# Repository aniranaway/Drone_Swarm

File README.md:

# Autonomous UWB Drone Swarm

A fully custom, low-level embedded hardware and firmware platform designed for autonomous multi drone swarms. The system integrates custom STM32-based flight controller PCBs, coreless DC motor drive arrays for a micro quadcopter form factor, Ultra-Wideband (UWB) 3D spatial localization, and custom control stacks built entirely from first principles—bypassing off-the-shelf flight controllers and third-party firmware stacks like PX4 or Betaflight.

---
## Grand Objectives

* **Bare-Metal Flight Control Stack:** Implement real-time 6-DoF sensor fusion and cascaded PID control loops running directly on STM32 microcontrollers.
* **Advanced State Estimation:** Design and implement a custom Extended Kalman Filter (EKF) pipeline to fuse multi-sensor measurements (IMU, Barometer, UWB), effectively suppressing sensor noise and drift for precise real-time 6-DoF state estimation.
* **UWB Spatial Positioning:** Achieve indoor positioning and tracking using UWB hardware operating across fixed anchor networks.
* **Autonomous Swarm Dynamics:** Execute coordinated multi-agent formation flight, collision avoidance algorithms, and telemetry links managed via a custom ground control station.
* **Rigorous Systems Engineering:** Maintain end-to-end engineering discipline across the full lifecycle—from System Requirements Documents (SRD) and component analysis to PCB layout, manufacturing, and firmware deployment.

## Project Documentation
Detailed engineering decisions and specifications are broken down in the `docs/` directory:
* [System Requirements Document (SRD)](docs/system_requirements.md)
* [Component Selection Analysis](docs/component_selection_analysis.md)
* [Bill of Materials (BOM)](docs/bill_of_materials.md)

---
## Repository Structure
* **/docs** - System engineering documents, trade studies, and requirements.
* **/hardware** - KiCad/Altium schematic captures and PCB layout files.
* **/firmware** - STM32 C/C++ application logic (CMake/Ninja toolchain).

## Development Roadmap

This project follows a structured hardware-software co-design lifecycle, progressing from systems engineering and hardware fabrication to low-level control, state estimation, and multi-agent coordination:

- [X] **Phase 1: Requirements & Component Selection** *(Completed)*  
  Establish System Requirements Documents (SRD), execute trade studies for core components (MCU, IMU, UWB, Power), and calculate mass/power budgets.

- [X] **Phase 2: Schematic Capture & Circuit Design**  *(Completed)* 
  Design power regulation, coreless motor MOSFET drive arrays, RF layout rules for radio, SWD interfaces, sensor layouts, and dedicated test pads.

- [ ] **Phase 3: PCB Layout, Manufacturing & Board Bring-Up**  (In Progress)
  Perform 4-layer PCB layout with impedance matching, manage fabrication/assembly, and execute board bring-up (power rail verification, current draw checks, and SWD flashing).

- [ ] **Phase 4: Low-Level Drivers & Telemetry Baseline**  
  Develop register-level/HAL SPI drivers for the IMU, I2C drivers for the barometer, PWM timer outputs for motor control, UART telemetry output, and status LED error handlers.

- [ ] **Phase 5: Airframe Assembly & Hardware Integration**  
  Mount flight controllers to micro frames, wire motor connections, calibrate motor spin directions, and verify physical center of mass.

- [ ] **Phase 6: Advanced State Estimation & Flight Control**  
  Implement digital low-pass filtering, build a custom Extended Kalman Filter (EKF) pipeline for IMU/Baro/UWB fusion, write cascaded PID controllers, and perform tethered flight tuning.

- [ ] **Phase 7: Swarm Simulation & Waypoint Planning**  
  Develop simulation frameworks and Ground Control Station (GCS) telemetry interfaces to validate trajectory generation and collision avoidance prior to physical swarm deployment.

- [ ] **Phase 8: UWB Infrastructure & Multi-Agent Setup**  
  Deploy and calibrate fixed indoor UWB anchors, assemble secondary flight hardware, and establish inter-node wireless communications.

- [ ] **Phase 9: Swarm Coordination & Autonomous Flight**  
  Execute decentralized/centralized swarm algorithms for coordinated formation flight, multi-agent pathing, and real-time telemetry tracking.

---
## Core Toolchain & Software Stack
* **GNU Arm Embedded Toolchain (`arm-none-eabi-gcc`)** — Cross-compiler toolchain used to compile bare-metal C/C++ application logic into ARM Cortex-M machine code.
* **CMake** — Meta-build system used to manage cross-compilation targets, include directories, linker scripts (`.ld`), and hardware macros in a clean, maintainable structure.
* **Ninja** — High-speed build system executed by CMake to handle fast, parallelized incremental compilation.
* **STM32CubeMX** — Graphical initialization utility used to configure MCU clock trees, pin assignments, and hardware peripherals (SPI, I2C, UART, TIM) while generating isolated HAL setup files.
* **OpenOCD** — Open On-Chip Debugger used to flash binary targets (`.elf`/`.hex`) to the STM32 MCU and provide a live GDB server over Serial Wire Debug (SWD) via ST-LINK.
* **VS Code & Cortex-Debug** — Primary IDE environment leveraging the Cortex-Debug extension for hardware breakpoints, register inspection, and integrated CMake builds.

---
## Core Hardware Stack
* **Microcontroller:** (In Progress - See Component Selection Analysis)
* **Spatial Positioning:** (In Progress - See Component Selection Analysis)
* **IMU:** (In Progress - See Component Selection Analysis)
* **Barometer:** (In Progress - See Component Selection Analysis)
* **Power:** (In Progress - See Component Selection Analysis)

---
## Getting Started
*(Instructions for cloning, compiling with CMake, and flashing the STM32 will go here).*

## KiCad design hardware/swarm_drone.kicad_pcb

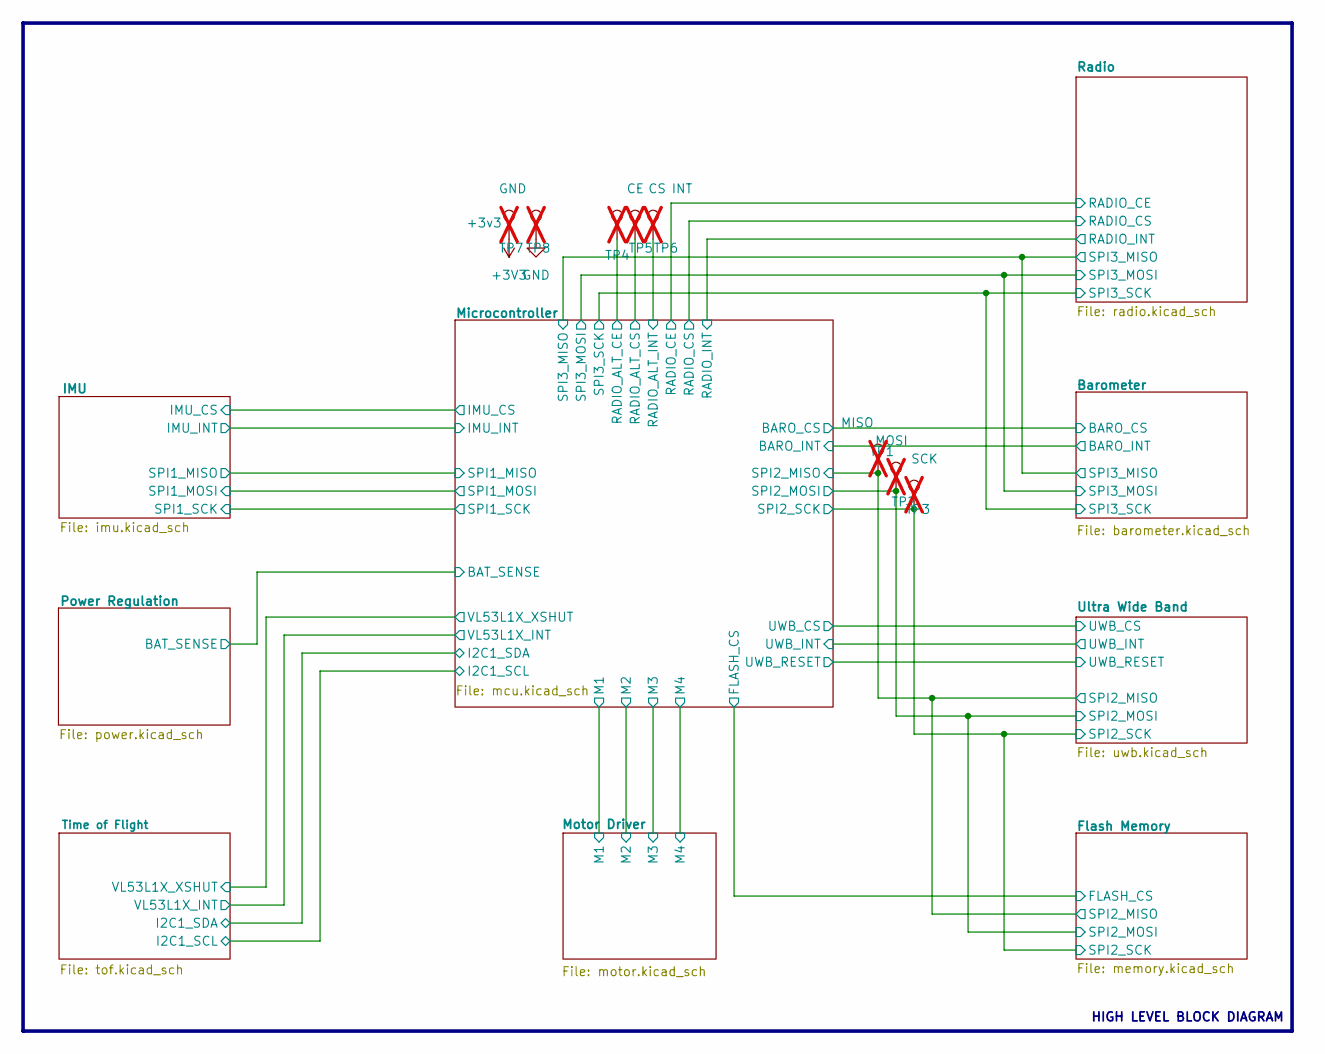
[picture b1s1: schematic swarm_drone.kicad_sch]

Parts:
TP1: MISO; TestPoint_Pad_1.0x1.0mm; not fitted
TP2: MOSI; TestPoint_Pad_1.0x1.0mm; not fitted
TP3: SCK; TestPoint_Pad_1.0x1.0mm; not fitted
TP4: CE; TestPoint_Pad_1.0x1.0mm; not fitted
TP5: CS; TestPoint_Pad_1.0x1.0mm; not fitted
TP6: INT; TestPoint_Pad_1.0x1.0mm; not fitted
TP7: +3v3; TestPoint_Pad_1.0x1.0mm; not fitted
TP8: GND; TestPoint_Pad_1.0x1.0mm; not fitted

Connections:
+3V3: TP7.1 (1_1); also elsewhere on the board
/Flash Memory/SPI2_MISO: TP1.1 (1_1); also elsewhere on the board
/Flash Memory/SPI2_MOSI: TP2.1 (1_1); also elsewhere on the board
/Flash Memory/SPI2_SCK: TP3.1 (1_1); also elsewhere on the board
/Microcontroller/RADIO_ALT_CE: TP4.1 (1_1); also elsewhere on the board
/Microcontroller/RADIO_ALT_CS: TP5.1 (1_1); also elsewhere on the board
/Microcontroller/RADIO_ALT_INT: TP6.1 (1_1); also elsewhere on the board
GND: TP8.1 (1_1); also elsewhere on the board

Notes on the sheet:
HIGH LEVEL BLOCK DIAGRAM

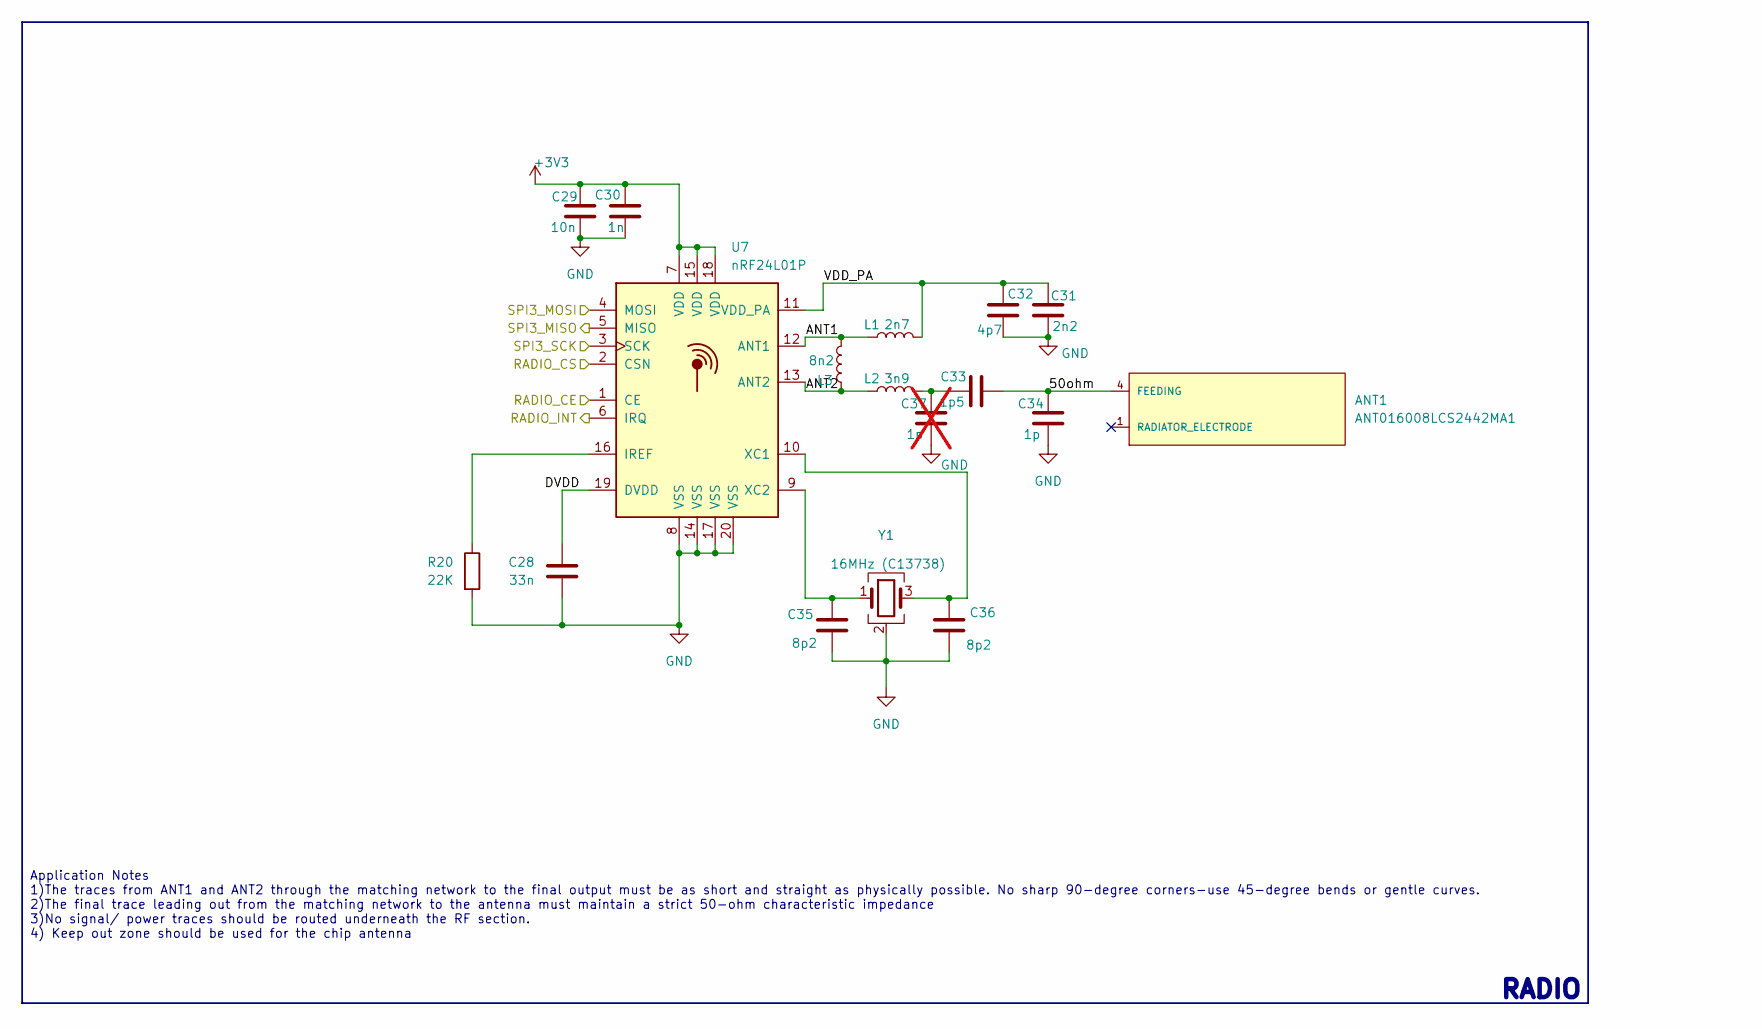
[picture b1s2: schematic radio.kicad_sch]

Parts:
ANT1: ANT016008LCS2442MA1; ANT_ANT016008LCS2442MA1; PARTREV sep 2016; LCSC C76585
C28: 33n; C_0603_1608Metric; LCSC C21117
C29: 10n; C_0402_1005Metric; LCSC C15195
C30: 1n; C_0402_1005Metric; LCSC C1523
C31: 2n2; C_0603_1608Metric; LCSC C1604
C32: 4p7; C_0402_1005Metric; LCSC C1569
C33: 1p5; C_0402_1005Metric; LCSC C1552
C34: 1p; C_0402_1005Metric; LCSC C1550
C35, C36: 8p2; C_0402_1005Metric; LCSC C1579
C37: 1p; C_0402_1005Metric; not fitted
L1: 2n7; L_0402_1005Metric
L2: 3n9; L_0402_1005Metric
L3: 8n2; L_0402_1005Metric
R20: 22K; R_0402_1005Metric; LCSC C25768
U7: nRF24L01P; QFN-20-1EP_4x4mm_P0.5mm_EP2.5x2.5mm; LCSC C8791
Y1: 16MHz (C13738); Crystal_SMD_3225-4Pin_3.2x2.5mm; LCSC C13738

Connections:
+3V3: C29.1, C30.1, U7.7 (VDD), U7.15 (VDD), U7.18 (VDD); also elsewhere on the board
/Barometer/SPI3_MISO: U7.5 (MISO); also elsewhere on the board
/Barometer/SPI3_MOSI: U7.4 (MOSI); also elsewhere on the board
/Barometer/SPI3_SCK: U7.3 (SCK); also elsewhere on the board
/Microcontroller/RADIO_CE: U7.1 (CE); also elsewhere on the board
/Microcontroller/RADIO_CS: U7.2 (CSN); also elsewhere on the board
/Microcontroller/RADIO_INT: U7.6 (IRQ); also elsewhere on the board
/Radio/50ohm: ANT1.4 (FEEDING_4), C33.2, C34.2
/Radio/ANT1: L1.1, L3.2, U7.12 (ANT1)
/Radio/ANT2: L2.1, L3.1, U7.13 (ANT2)
/Radio/DVDD: C28.1, U7.19 (DVDD)
/Radio/VDD_PA: C31.1, C32.1, L1.2, U7.11 (VDD_PA)
GND: C28.2, C29.2, C30.2, C31.2, C32.2, C34.1, C35.2, C36.2, C37.1, R20.2, U7.8 (VSS), U7.14 (VSS), U7.17 (VSS), U7.20 (VSS), Y1.2 (G), Y1.4 (G); also elsewhere on the board
unnamed: C33.1, C37.2, L2.2
unnamed: R20.1, U7.16 (IREF)
unnamed: C36.1, U7.10 (XC1), Y1.3
unnamed: C35.1, U7.9 (XC2), Y1.1

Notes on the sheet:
RADIO
Application Notes 1)The traces from ANT1 and ANT2 through the matching network to the final output must be as short and straight as physically possible. No sharp 90-degree corners-use 45-degree bends or gentle curves. 2)The final trace leading out from the matching network to the antenna must maint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

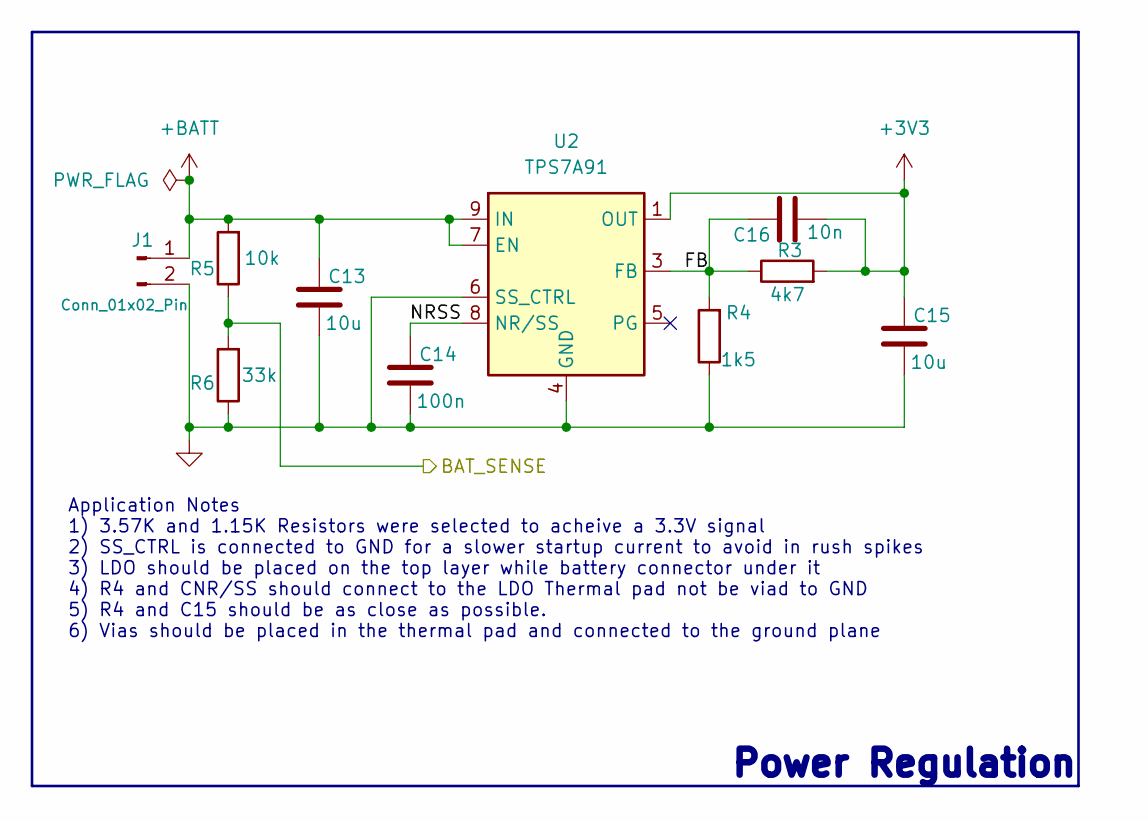
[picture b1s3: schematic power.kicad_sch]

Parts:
C13, C15: 10u; C_0603_1608Metric; LCSC C19702
C14: 100n; C_0402_1005Metric; LCSC C1525
C16: 10n; C_0402_1005Metric; LCSC C15195
J1: Conn_01x02_Pin; JST_PH_S2B-PH-K_1x02_P2.00mm_Horizontal; LCSC C173752
R3: 4k7; R_0402_1005Metric; LCSC C25900
R4: 1k5; R_0402_1005Metric; LCSC C25867
R5: 10k; R_0402_1005Metric; LCSC C25744
R6: 33k; R_0402_1005Metric; LCSC C25779
U2: TPS7A91; Texas_S-PDSO-N10_EP1.2x2mm_ThermalVias; LCSC C969024

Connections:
+3V3: C15.1, C16.2, R3.2, U2.1 (OUT), U2.2 (OUT); also elsewhere on the board
+BATT: C13.1, J1.1, R5.2, U2.7 (EN), U2.9 (IN), U2.10 (IN); also elsewhere on the board
/Microcontroller/BAT_SENSE: R5.1, R6.2; also elsewhere on the board
/Power Regulation/FB: C16.1, R3.1, R4.2, U2.3 (FB)
/Power Regulation/NRSS: C14.1, U2.8 (NR/SS)
GND: C13.2, C14.2, C15.2, J1.2, R4.1, R6.1, U2.4 (GND), U2.6 (SS_CTRL), U2.11 (GND); also elsewhere on the board

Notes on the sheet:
Application Notes 1) 3.57K and 1.15K Resistors were selected to acheive a 3.3V signal 2) SS_CTRL is connected to GND for a slower startup current to avoid in rush spikes 3) LDO should be placed on the top layer while battery connector under it 4) R4 and CNR/SS should connect to the LDO Thermal pad 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
Power Regulation

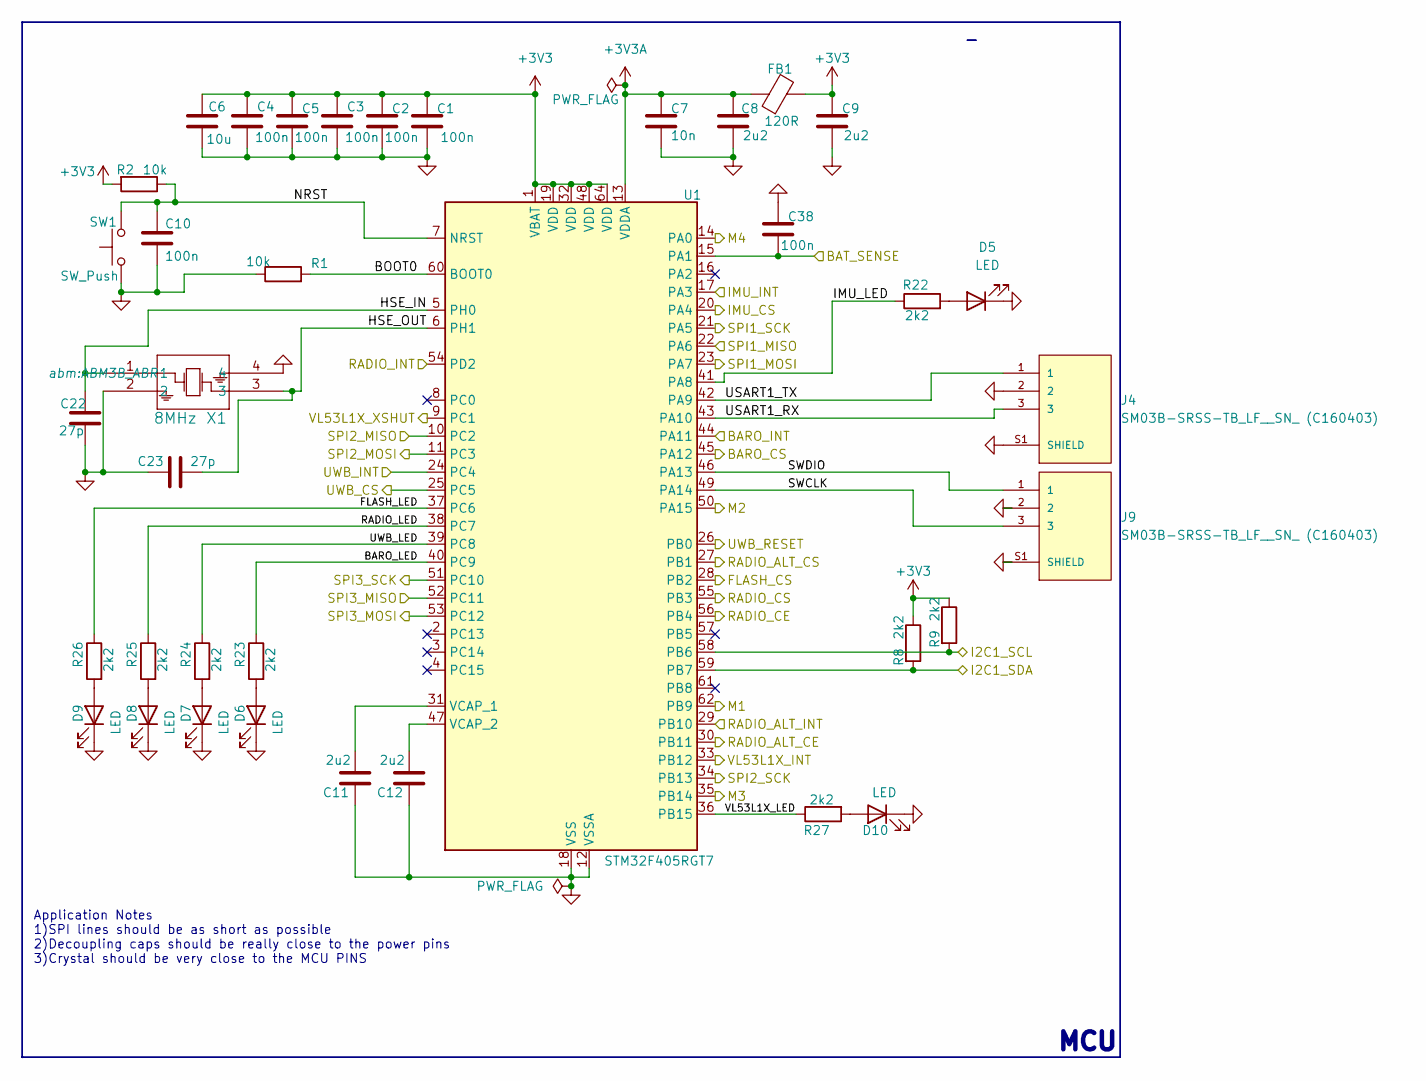
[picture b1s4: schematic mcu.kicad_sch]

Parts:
C1, C2, C3, C4, C5, C10, C38: 100n; C_0402_1005Metric; LCSC C1525
C6: 10u; C_0603_1608Metric; LCSC C19702
C7: 10n; C_0402_1005Metric; LCSC C15195
C8, C9, C11, C12: 2u2; C_0402_1005Metric; LCSC C12530
C22, C23: 27p; C_0402_1005Metric; LCSC C1557
D5, D6, D7, D8, D9, D10: LED; LED_0603_1608Metric; LCSC C2286
FB1: 120R; L_0603_1608Metric; LCSC C14709
J4, J9: SM03B-SRSS-TB_LF__SN_ (C160403); JST_SM03B-SRSS-TB_LF__SN_; LCSC C160403
R1, R2: 10k; R_0402_1005Metric; LCSC C25744
R8, R9, R22, R23, R24, R25, R26, R27: 2k2; R_0402_1005Metric; LCSC C25879
SW1: SW_Push; SW_SPST_TS-1088-xR020; LCSC C720477
U1: STM32F405RGT7; LQFP-64_10x10mm_P0.5mm; LCSC C1337199
X1: 8MHz; ABM3B_ABR; LCSC C83312

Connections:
+3V3: C1.1, C2.1, C3.1, C4.1, C5.1, C6.1, C9.1, FB1.2, R2.2, R8.1, R9.1, U1.1 (VBAT), U1.19 (VDD), U1.32 (VDD), U1.48 (VDD), U1.64 (VDD); also elsewhere on the board
+3V3A: C7.1, C8.1, FB1.1, U1.13 (VDDA)
/Barometer/BARO_CS: U1.45 (PA12); also elsewhere on the board
/Barometer/BARO_INT: U1.44 (PA11); also elsewhere on the board
/Barometer/SPI3_MISO: U1.52 (PC11); also elsewhere on the board
/Barometer/SPI3_MOSI: U1.53 (PC12); also elsewhere on the board
/Barometer/SPI3_SCK: U1.51 (PC10); also elsewhere on the board
/Flash Memory/FLASH_CS: U1.28 (PB2); also elsewhere on the board
/Flash Memory/SPI2_MISO: U1.10 (PC2); also elsewhere on the board
/Flash Memory/SPI2_MOSI: U1.11 (PC3); also elsewhere on the board
/Flash Memory/SPI2_SCK: U1.34 (PB13); also elsewhere on the board
/IMU/IMU_CS: U1.20 (PA4); also elsewhere on the board
/IMU/IMU_INT: U1.17 (PA3); also elsewhere on the board
/IMU/SPI1_MISO: U1.22 (PA6); also elsewhere on the board
/IMU/SPI1_MOSI: U1.23 (PA7); also elsewhere on the board
/IMU/SPI1_SCK: U1.21 (PA5); also elsewhere on the board
/Microcontroller/BARO_LED: R23.1, U1.40 (PC9)
/Microcontroller/BAT_SENSE: C38.2, U1.15 (PA1); also elsewhere on the board
/Microcontroller/BOOT0: R1.2, U1.60 (BOOT0)
/Microcontroller/FLASH_LED: R26.1, U1.37 (PC6)
/Microcontroller/HSE_IN: C22.1, U1.5 (PH0), X1.1
/Microcontroller/HSE_OUT: C23.2, U1.6 (PH1), X1.3
/Microcontroller/I2C1_SCL: R9.2, U1.58 (PB6); also elsewhere on the board
/Microcontroller/I2C1_SDA: R8.2, U1.59 (PB7); also elsewhere on the board
/Microcontroller/IMU_LED: R22.1, U1.41 (PA8)
/Microcontroller/M1: U1.62 (PB9); also elsewhere on the board
/Microcontroller/M2: U1.50 (PA15); also elsewhere on the board
/Microcontroller/M3: U1.35 (PB14); also elsewhere on the board
/Microcontroller/M4: U1.14 (PA0); also elsewhere on the board
/Microcontroller/NRST: C10.1, R2.1, SW1.2, U1.7 (NRST)
/Microcontroller/RADIO_ALT_CE: U1.30 (PB11); also elsewhere on the board
/Microcontroller/RADIO_ALT_CS: U1.27 (PB1); also elsewhere on the board
/Microcontroller/RADIO_ALT_INT: U1.29 (PB10); also elsewhere on the board
/Microcontroller/RADIO_CE: U1.56 (PB4); also elsewhere on the board
/Microcontroller/RADIO_CS: U1.55 (PB3); also elsewhere on the board
/Microcontroller/RADIO_INT: U1.54 (PD2); also elsewhere on the board
/Microcontroller/RADIO_LED: R25.1, U1.38 (PC7)
/Microcontroller/SWCLK: J9.3, U1.49 (PA14)
/Microcontroller/SWDIO: J9.1, U1.46 (PA13)
/Microcontroller/USART1_RX: J4.3, U1.43 (PA10)
/Microcontroller/USART1_TX: J4.1, U1.42 (PA9)
/Microcontroller/UWB_CS: U1.25 (PC5); also elsewhere on the board
/Microcontroller/UWB_INT: U1.24 (PC4); also elsewhere on the board
/Microcontroller/UWB_LED: R24.1, U1.39 (PC8)
/Microcontroller/UWB_RESET: U1.26 (PB0); also elsewhere on the board
/Microcontroller/VL53L1X_INT: U1.33 (PB12); also elsewhere on the board
/Microcontroller/VL53L1X_LED: R27.1, U1.36 (PB15)
/Microcontroller/VL53L1X_XSHUT: U1.9 (PC1); also elsewhere on the board
GND: C1.2, C2.2, C3.2, C4.2, C5.2, C6.2, C7.2, C8.2, C9.2, C10.2, C11.1, C12.1, C22.2, C23.1, C38.1, D5.1 (K), D6.1 (K), D7.1 (K), D8.1 (K), D9.1 (K), D10.1 (K), J4.2, J4.S1 (SHIELD), J4.S2 (SHIELD), J9.2, J9.S1 (SHIELD), J9.S2 (SHIELD), R1.1, SW1.1, U1.12 (VSSA), U1.18 (VSS), U1.63 (VSS), X1.2, X1.4; also elsewhere on the board
unnamed: D5.2 (A), R22.2
unnamed: D6.2 (A), R23.2
unnamed: D7.2 (A), R24.2
unnamed: D8.2 (A), R25.2
unnamed: D9.2 (A), R26.2
unnamed: D10.2 (A), R27.2
unnamed: C11.2, U1.31 (VCAP_1)
unnamed: C12.2, U1.47 (VCAP_2)

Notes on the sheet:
Application Notes 1)SPI lines should be as short as possible 2)Decoupling caps should be really close to the power pins 3)Crystal should be very close to the MCU PINS
MCU

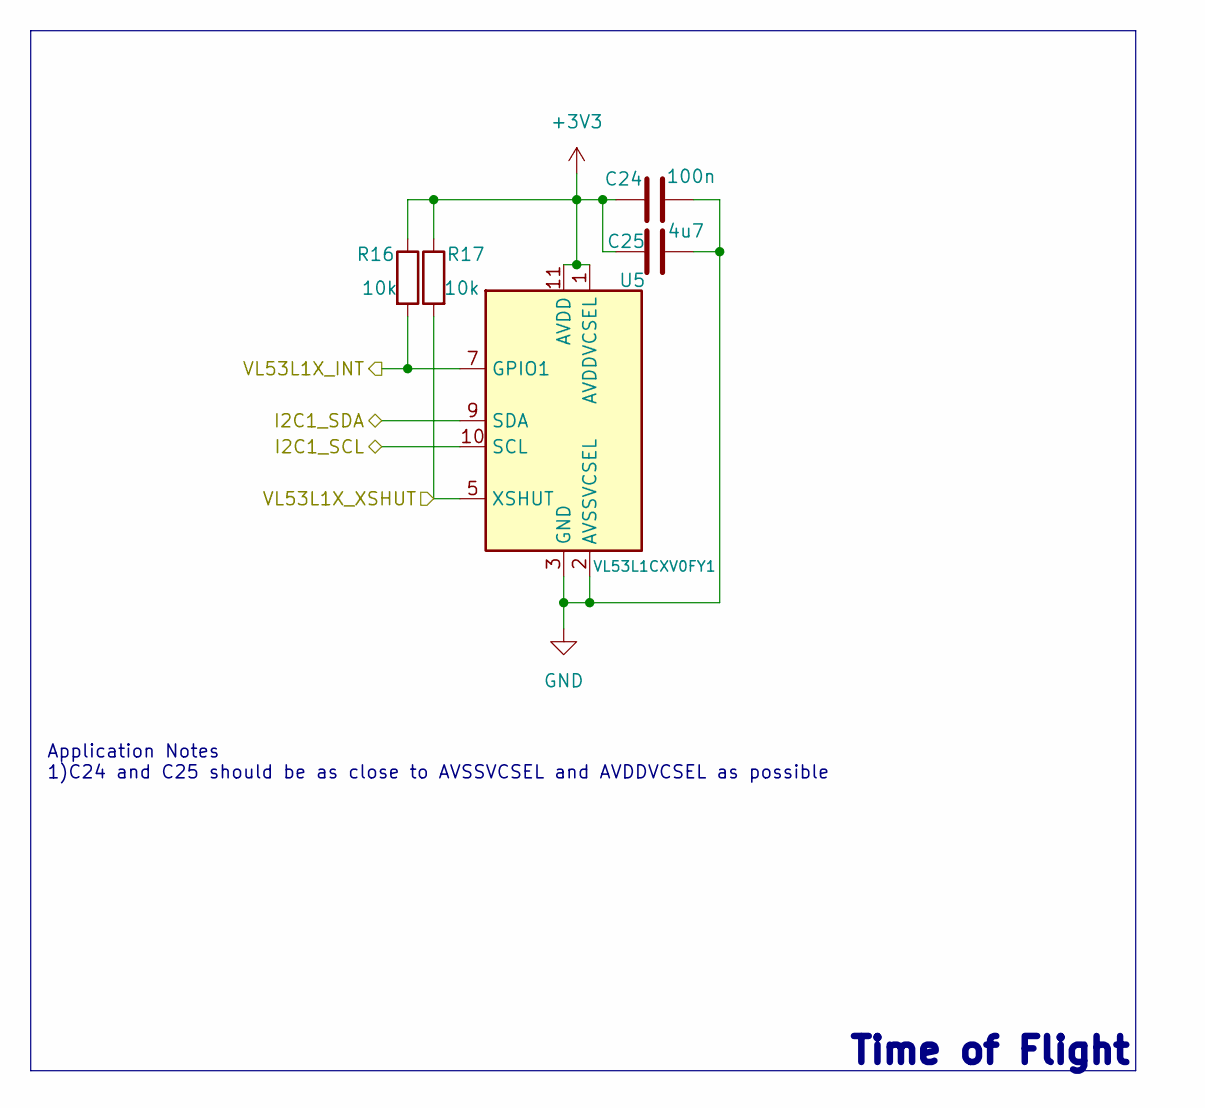
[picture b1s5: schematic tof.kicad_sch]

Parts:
C24: 100n; C_0402_1005Metric; LCSC C1525
C25: 4u7; C_0603_1608Metric; LCSC C19666
R16, R17: 10k; R_0402_1005Metric; LCSC C25744
U5: VL53L1CXV0FY1; ST_VL53L1x; LCSC C190004

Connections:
+3V3: C24.1, C25.1, R16.1, R17.1, U5.1 (AVDDVCSEL), U5.11 (AVDD); also elsewhere on the board
/Microcontroller/I2C1_SCL: U5.10 (SCL); also elsewhere on the board
/Microcontroller/I2C1_SDA: U5.9 (SDA); also elsewhere on the board
/Microcontroller/VL53L1X_INT: R16.2, U5.7 (GPIO1); also elsewhere on the board
/Microcontroller/VL53L1X_XSHUT: R17.2, U5.5 (XSHUT); also elsewhere on the board
GND: C24.2, C25.2, U5.2 (AVSSVCSEL), U5.3 (GND), U5.4 (GND), U5.6 (GND), U5.12 (GND); also elsewhere on the board

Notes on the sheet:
Application Notes 1)C24 and C25 should be as close to AVSSVCSEL and AVDDVCSEL as possible
Time of Flight

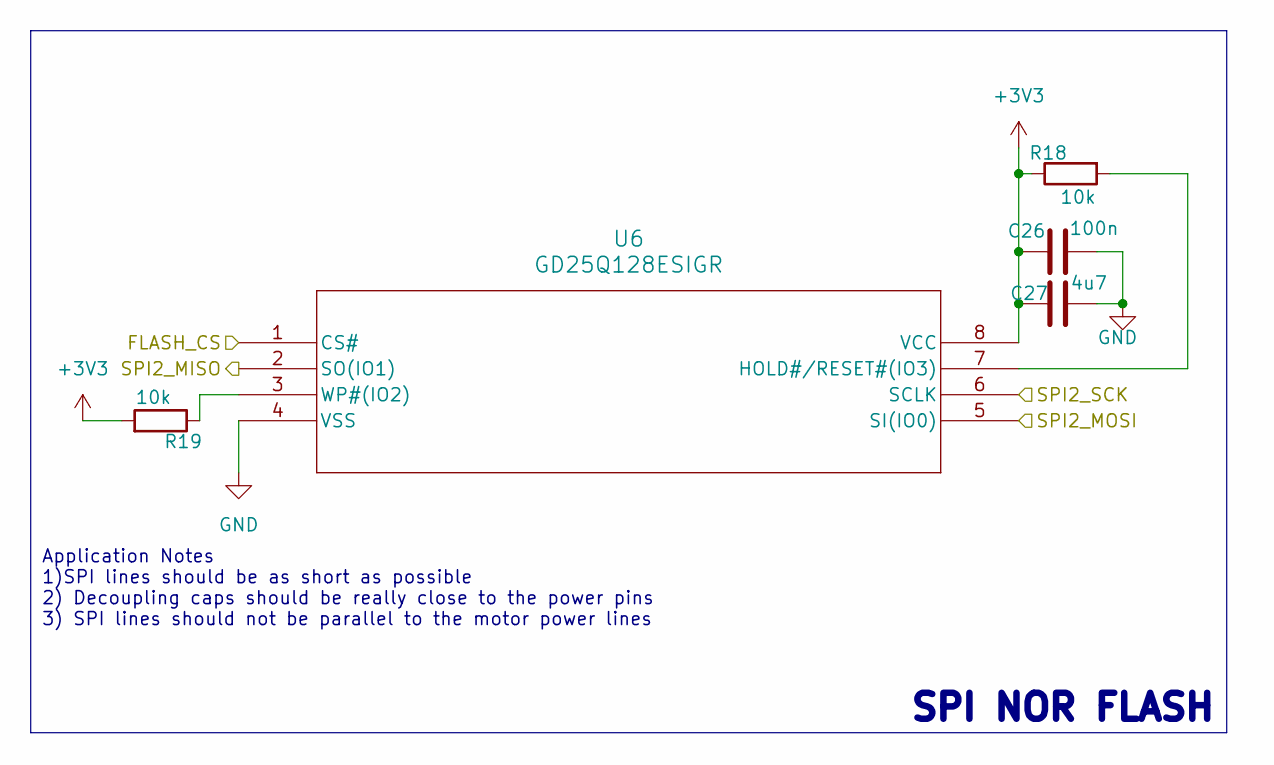
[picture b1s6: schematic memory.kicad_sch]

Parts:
C26: 100n; C_0402_1005Metric; LCSC C1525
C27: 4u7; C_0603_1608Metric; LCSC C19666
R18, R19: 10k; R_0402_1005Metric; LCSC C25744
U6: GD25Q128ESIGR; SOP8_208MIL_GDV; LCSC C2928891

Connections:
+3V3: C26.1, C27.1, R18.1, R19.2, U6.8 (VCC); also elsewhere on the board
/Flash Memory/FLASH_CS: U6.1 (CS#); also elsewhere on the board
/Flash Memory/SPI2_MISO: U6.2 (SO(IO1)); also elsewhere on the board
/Flash Memory/SPI2_MOSI: U6.5 (SI(IO0)); also elsewhere on the board
/Flash Memory/SPI2_SCK: U6.6 (SCLK); also elsewhere on the board
GND: C26.2, C27.2, U6.4 (VSS); also elsewhere on the board
unnamed: R18.2, U6.7 (HOLD#/RESET#(IO3))
unnamed: R19.1, U6.3 (WP#(IO2))

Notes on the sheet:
SPI NOR FLASH
Application Notes 1)SPI lines should be as short as possible 2) Decoupling caps should be really close to the power pins 3) SPI lines should not be parallel to the motor power lines

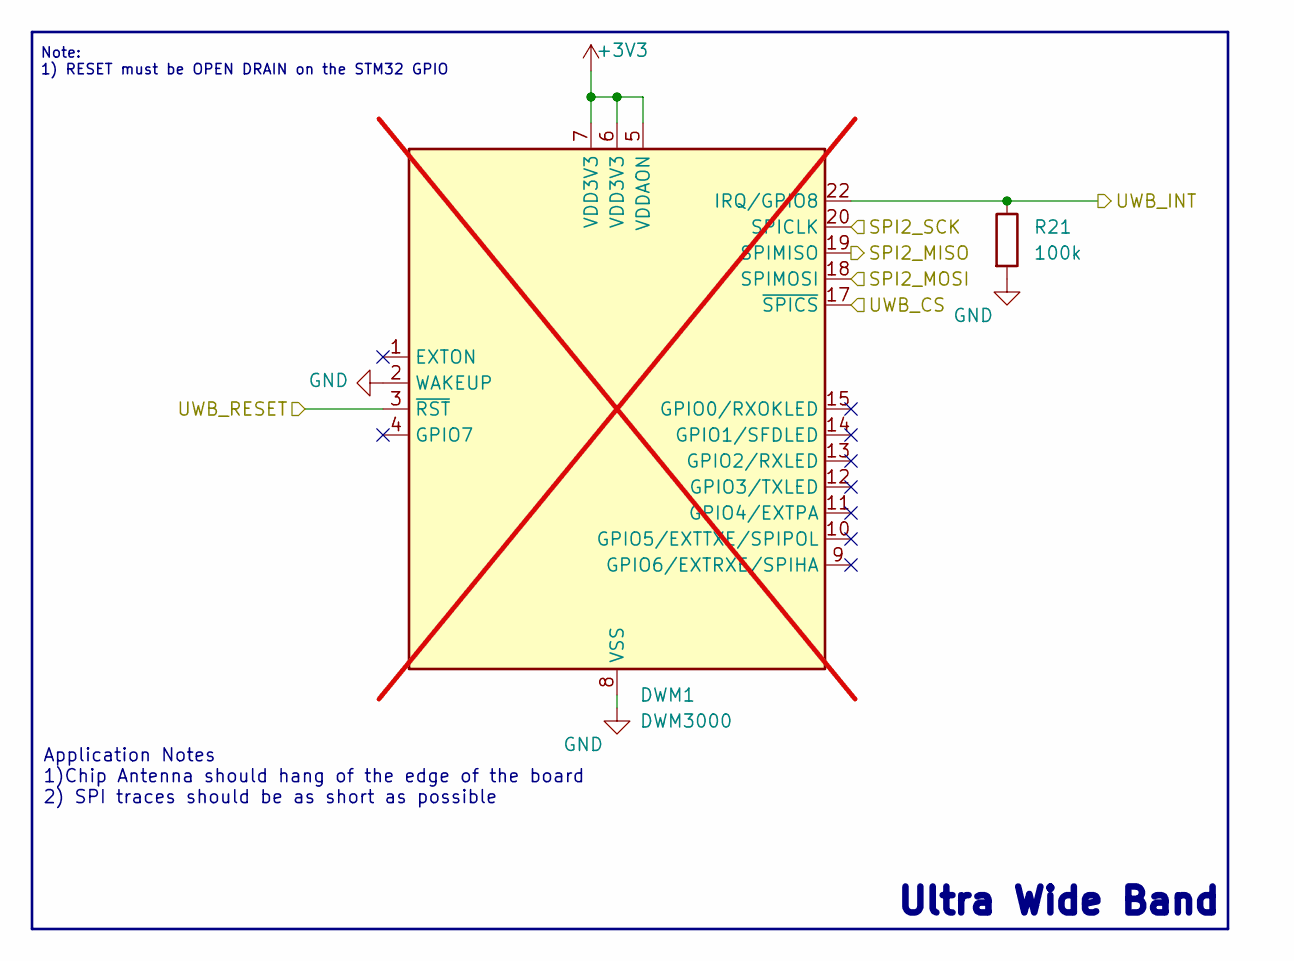
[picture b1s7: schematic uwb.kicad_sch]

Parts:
DWM1: DWM3000; DWM1000; not fitted
R21: 100k; R_0402_1005Metric; LCSC C25741

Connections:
+3V3: DWM1.5 (VDDAON), DWM1.6 (VDD3V3), DWM1.7 (VDD3V3); also elsewhere on the board
/Flash Memory/SPI2_MISO: DWM1.19 (SPIMISO); also elsewhere on the board
/Flash Memory/SPI2_MOSI: DWM1.18 (SPIMOSI); also elsewhere on the board
/Flash Memory/SPI2_SCK: DWM1.20 (SPICLK); also elsewhere on the board
/Microcontroller/UWB_CS: DWM1.17 (~SPICS); also elsewhere on the board
/Microcontroller/UWB_INT: DWM1.22 (IRQ/GPIO8), R21.1; also elsewhere on the board
/Microcontroller/UWB_RESET: DWM1.3 (~RST); also elsewhere on the board
GND: DWM1.2 (WAKEUP), DWM1.8 (VSS), DWM1.16 (VSS), DWM1.21 (VSS), DWM1.23 (VSS), DWM1.24 (VSS), R21.2; also elsewhere on the board

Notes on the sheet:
Application Notes 1)Chip Antenna should hang of the edge of the board 2) SPI traces should be as short as possible
Ultra Wide Band
Note: 1) RESET must be OPEN DRAIN on the STM32 GPIO

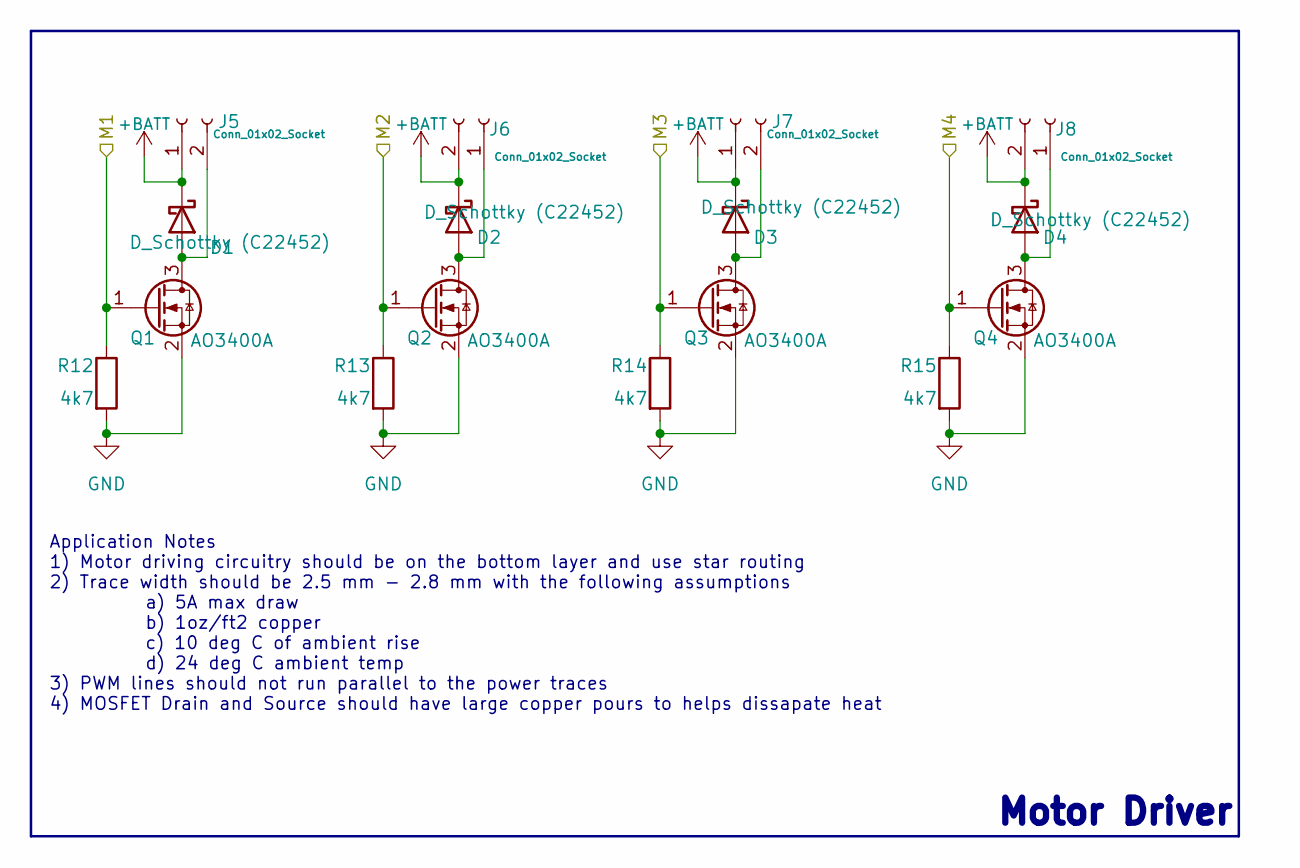
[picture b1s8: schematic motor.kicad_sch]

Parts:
D1, D2, D3, D4: D_Schottky (C22452); D_SMA; LCSC C22452
J5, J6, J7, J8: Conn_01x02_Socket; JST_S2B-ZR-3.4_LF__SN_; LCSC C160729
Q1, Q2, Q3, Q4: AO3400A; SOT-23; LCSC C20917
R12, R13, R14, R15: 4k7; R_0402_1005Metric; LCSC C25900

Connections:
+BATT: D1.1 (K), D2.1 (K), D3.1 (K), D4.1 (K), J5.1, J6.2, J7.1, J8.2; also elsewhere on the board
/Microcontroller/M1: Q1.1 (G), R12.1; also elsewhere on the board
/Microcontroller/M2: Q2.1 (G), R13.1; also elsewhere on the board
/Microcontroller/M3: Q3.1 (G), R14.1; also elsewhere on the board
/Microcontroller/M4: Q4.1 (G), R15.1; also elsewhere on the board
GND: Q1.2 (S), Q2.2 (S), Q3.2 (S), Q4.2 (S), R12.2, R13.2, R14.2, R15.2; also elsewhere on the board
unnamed: D1.2 (A), J5.2, Q1.3 (D)
unnamed: D2.2 (A), J6.1, Q2.3 (D)
unnamed: D3.2 (A), J7.2, Q3.3 (D)
unnamed: D4.2 (A), J8.1, Q4.3 (D)

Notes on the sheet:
Application Notes 1) Motor driving circuitry should be on the bottom layer and use star routing 2) Trace width should be 2.5 mm - 2.8 mm with the following assumptions a) 5A max draw b) 1oz/ft2 copper c) 10 deg C of ambient rise d) 24 deg C ambient temp 3) PWM lines should not run parallel to the p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
Motor Driver

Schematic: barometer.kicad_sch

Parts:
C20, C21: 100n; C_0402_1005Metric; LCSC C1525
U4: BMP581; QFN10_BMP581_BOS; LCSC C5362283

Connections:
+3V3: C20.1, C21.1, U4.1 (VDDIO), U4.10 (VDD); also elsewhere on the board
/Barometer/BARO_CS: U4.6 (CSB); also elsewhere on the board
/Barometer/BARO_INT: U4.7 (INT); also elsewhere on the board
/Barometer/SPI3_MISO: U4.5 (SDO); also elsewhere on the board
/Barometer/SPI3_MOSI: U4.4 (SDI); also elsewhere on the board
/Barometer/SPI3_SCK: U4.2 (SCK); also elsewhere on the board
GND: C20.2, C21.2, U4.3 (VSS), U4.8 (VSS), U4.9 (VSS); also elsewhere on the board

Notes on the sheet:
Application Notes 1) Barometer should be placed on the central axis of the PCB to avoid pressure drops from the motors 2) Barometer should be placed away from high heat components 3) Barometer should not be placed near the very edge of the PCB to avoid twisiting forces adding noise
Barometer

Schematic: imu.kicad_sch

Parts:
C17: 100n; C_0402_1005Metric; LCSC C1525
C18: 2u2; C_0402_1005Metric; LCSC C12530
C19: 10n; C_0402_1005Metric; LCSC C15195
R7: 10k; R_0402_1005Metric; LCSC C25744
U3: ICM-42688-P; PQFN50P300X250X97-14N; PARTREV 1.2; LCSC C1850418

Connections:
+3V3: C17.1, C18.1, C19.1, R7.2, U3.5 (VDDIO), U3.8 (VDD); also elsewhere on the board
/IMU/IMU_CS: R7.1, U3.12 (AP_CS); also elsewhere on the board
/IMU/IMU_INT: U3.4 (INT1/INT); also elsewhere on the board
/IMU/SPI1_MISO: U3.1 (AP_SDO/AP_AD0); also elsewhere on the board
/IMU/SPI1_MOSI: U3.14 (AP_SDA/AP_SDIO/AP_SDI); also elsewhere on the board
/IMU/SPI1_SCK: U3.13 (AP_SCL/AP_SCLK); also elsewhere on the board
GND: C17.2, C18.2, C19.2, U3.2 (RESV_2), U3.3 (RESV_3), U3.6 (GND), U3.7 (RESV_7), U3.9 (INT2/FSYNC/CLKIN), U3.10 (RESV_10), U3.11 (RESV_11); also elsewhere on the board

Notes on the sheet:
Application Notes 1) IMU Shoulde be placed as close to the geometric centre of the PCB as possible 2) IMU should not be placed near high heat components 3) decoupling caps should be placed very close to power pins
IMU

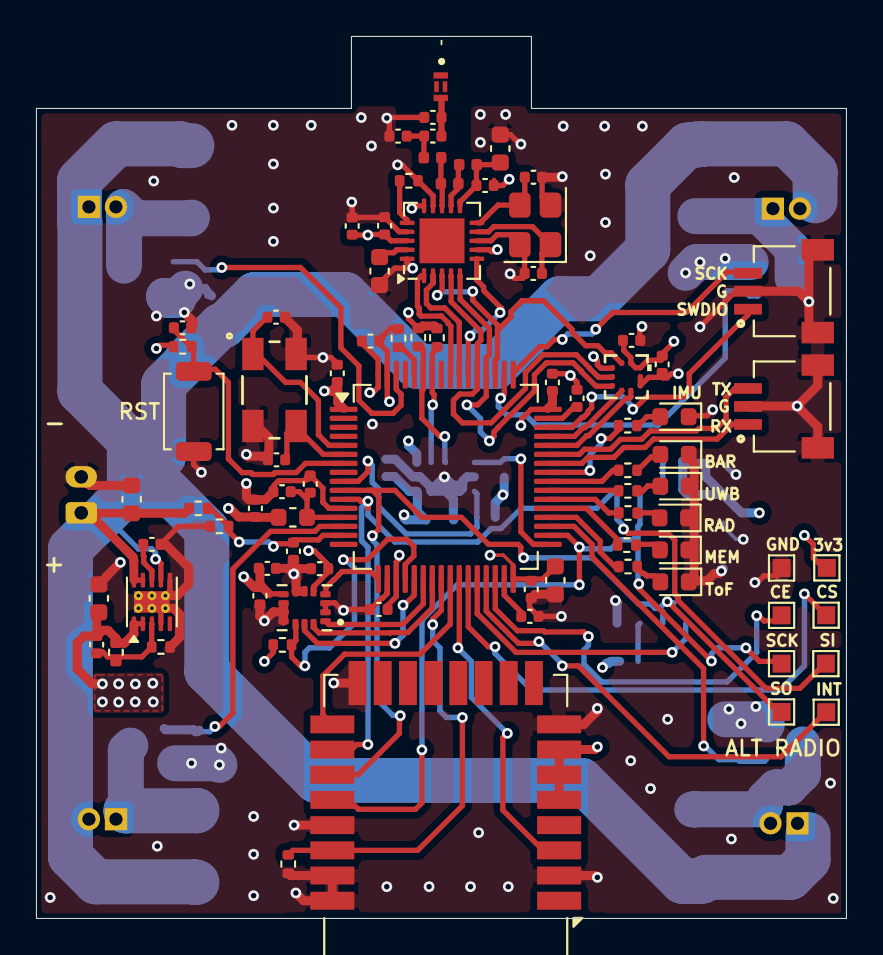
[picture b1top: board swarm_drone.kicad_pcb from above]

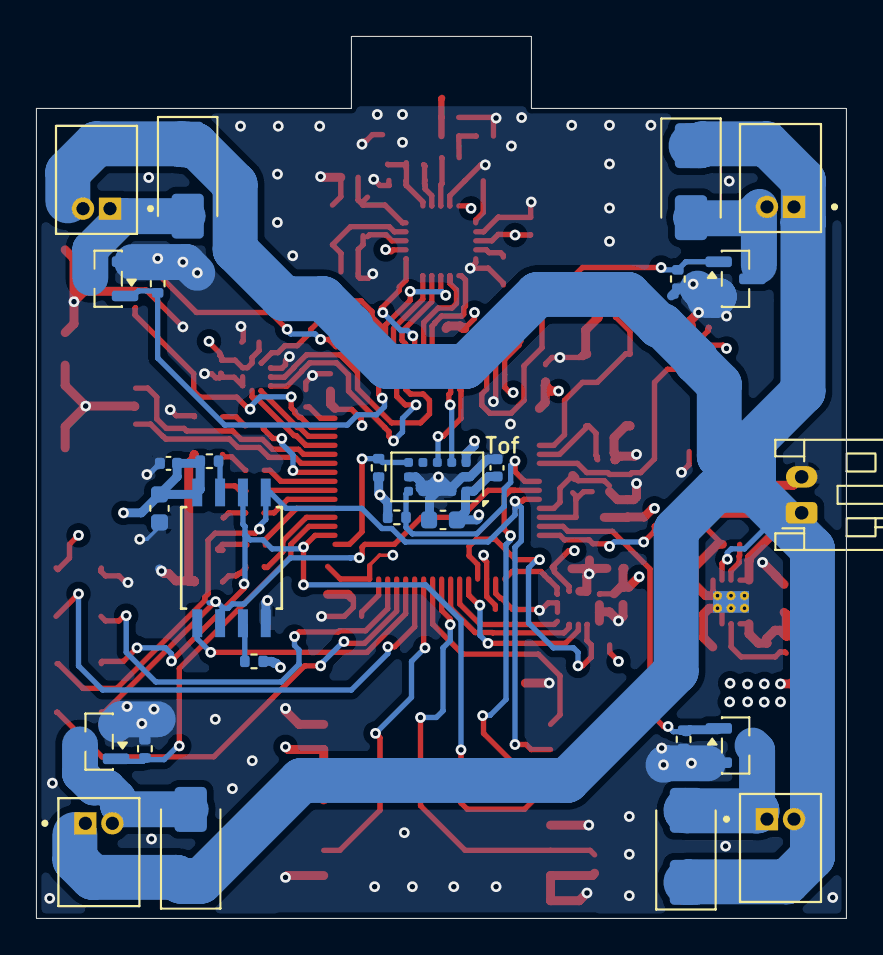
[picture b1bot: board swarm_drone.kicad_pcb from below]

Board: 4 copper layers, 45.0 x 49.0 mm, 108 parts (27 on the bottom side), 75 nets.
